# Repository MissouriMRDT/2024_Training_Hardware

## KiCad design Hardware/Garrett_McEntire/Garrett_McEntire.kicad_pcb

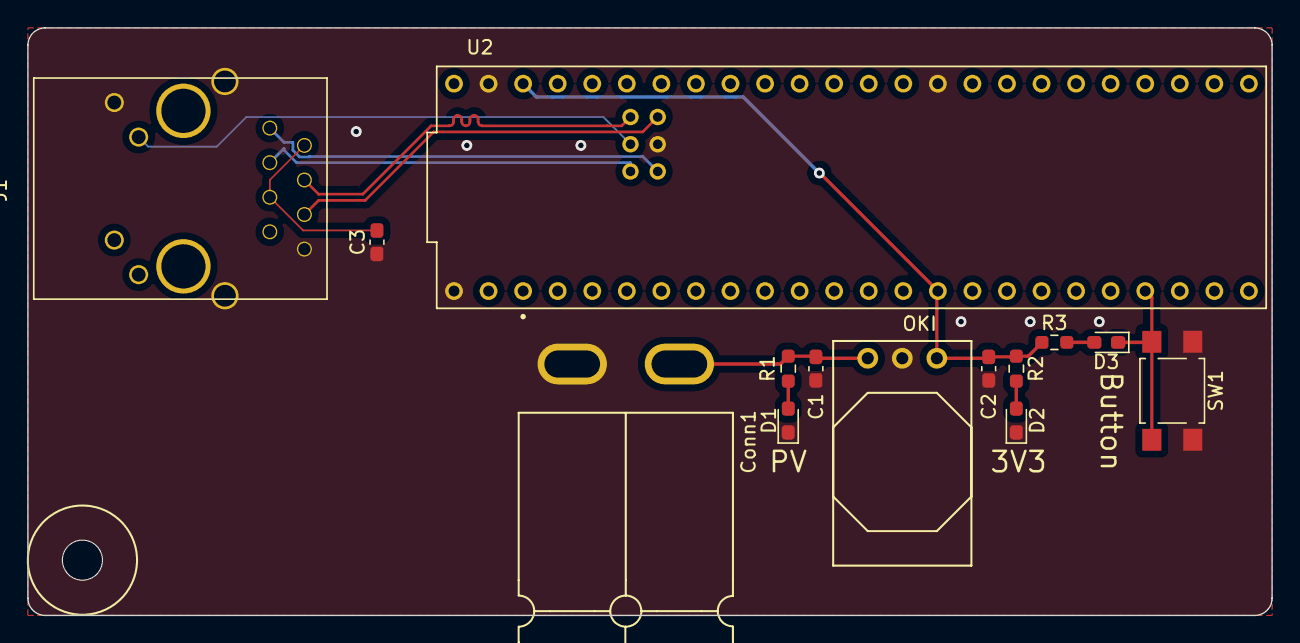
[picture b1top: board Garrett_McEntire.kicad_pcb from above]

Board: 2 copper layers, 91.4 x 43.2 mm, 14 parts (0 on the bottom side), 13 nets.

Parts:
C1, C2: 10uF; C_0603_1608Metric_Pad1.08x0.95mm_HandSolder
C3: 0.1uF; C_0603_1608Metric_Pad1.08x0.95mm_HandSolder
Conn1: AndersonPP; Square_Anderson_2_H_Side_By_Side_PV
D1, D2: Green; LED_0603_1608Metric_Pad1.05x0.95mm_HandSolder
D3: Blue; LED_0603_1608Metric_Pad1.05x0.95mm_HandSolder
J1: RJ45_LED_Shielded; RJ45_Teensy
R1: 3k; R_0603_1608Metric_Pad0.98x0.95mm_HandSolder
R2, R3: 120; R_0603_1608Metric_Pad0.98x0.95mm_HandSolder
SW1: SW_Push; SW_SPST_TL3305A
U1: OKI; OKI_Horizontal
U2: Teensy4.1_DEV-16771; Teensy_4_1_Ethernet

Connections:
+3V3: C2.1, R2.1, R3.1, U1.3 (Vo), U2.3.3V_1 (3.3V), U2.3.3V_2 (3.3V)
/R+: J1.4, U2.R+
/R-: J1.6, U2.R-
/T+: J1.1, U2.T+
/T-: J1.3, U2.T-
GND: C1.2, C2.2, C3.1, Conn1.1 (GND), D1.1 (K), D2.1 (K), J1.8, J1.9, J1.SH, SW1.1, U1.2 (GND), U2.GND1 (GND), U2.GND2 (GND), U2.GND3 (GND), U2.GND5 (GND)
unnamed: C3.2, J1.2, J1.5
unnamed: D1.2 (A), R1.2
unnamed: D2.2 (A), R2.2
unnamed: D3.2 (A), R3.2
unnamed: J1.10, U2.LED
PV: C1.1, Conn1.4 (PV+), R1.1, U1.1 (Vi)
Test_Button: D3.1 (K), SW1.2, U2.29 (TX7)
